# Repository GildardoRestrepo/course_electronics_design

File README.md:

# Diseño Electrónico — UPB

Este repositorio reúne todas las actividades del curso **Diseño Electrónico** (UPB). El curso combina una parte **teórica sobre inteligencia artificial** y una parte **práctica sobre IoT, sistemas embebidos y diseño electrónico**: firmware para ESP32, servidores MQTT, dashboards y diseño de PCB en KiCad.

**Autor:** Gildardo Estevan Restrepo Duque

## Actividades

| #   | Actividad                                                                                       | Carpeta                                                | Bitácora                                                               |
| --- | ----------------------------------------------------------------------------------------------- | ------------------------------------------------------ | ---------------------------------------------------------------------- |
| 01  | Conexión a Ubidots                                                                              | [`01_ubidots_connection`](01_ubidots_connection)       | [01_ubidots_connection.md](00_docs/01_ubidots_connection.md)           |
| 02  | Suscripción a Ubidots (downlinks)                                                               | [`02_ubidots_subscription`](02_ubidots_subscription)   | [02_ubidots_subscription.md](00_docs/02_ubidots_subscription.md)       |
| 03  | Access Point + servidor web                                                                     | [`03_webserver_accesspoint`](03_webserver_accesspoint) | [03_webserver_accesspoint.md](00_docs/03_webserver_accesspoint.md)     |
| 04  | Repositorio de entregables                                                                      | —                                                      | [04_repositorio_entregables.md](00_docs/04_repositorio_entregables.md) |
| 05  | MQTT local: Mosquitto + Node-RED                                                                | [`05_mqtt_local_nodered`](05_mqtt_local_nodered)       | [05_mqtt_local_nodered.md](00_docs/05_mqtt_local_nodered.md)           |
| 06  | MQTT en la nube: AWS + Mosquitto + Node-RED                                                     | [`06_mqtt_in_aws`](06_mqtt_in_aws)                     | [06_mqtt_in_aws.md](00_docs/06_mqtt_in_aws.md)                         |
| 08  | Introducción al flujo de trabajo en KiCad                                                       | [`08_kicad_flow_work`](08_kicad_flow_work)             | [08_kicad_flow_work.md](00_docs/08_kicad_flow_work.md)                 |
| 09  | Fuente de poder en KiCad                                                                        | [`09_power_supply`](09_power_supply)                   | [09_power_supply.md](00_docs/09_power_supply.md)                       |
| 10  | Diseño en 4 capas: datalogger ATmega328P                                                        | [`10_4layer_design`](10_4layer_design)                 | [10_4layer_design.md](00_docs/10_4layer_design.md)                     |
| 11  | Diseño de placa basada en ESP32:<br>Controlador de Conmutación para Semiconductores de Potencia | `11_final_esp32`                                       | [[11_gating_block_power_electronics]]                                  |

Cada bitácora de [`00_docs/`](00_docs) explica el objetivo, el montaje y cómo reproducir la práctica. Los valores reales de Wi-Fi, tokens y contraseñas no se versionan: cada proyecto trae un archivo de ejemplo (`secrets.h.example`) o marcadores para completar localmente.

La carpeta [`.claude/skills/kicad-flow`](.claude/skills/kicad-flow) contiene el flujo de trabajo para diseñar y verificar los proyectos de KiCad con Claude Code.

## Licencia

MIT. Ver [LICENSE](LICENSE).

---
## Enlaces
[[diseno_electronico_iot|Diseño Electrónico IoT]]

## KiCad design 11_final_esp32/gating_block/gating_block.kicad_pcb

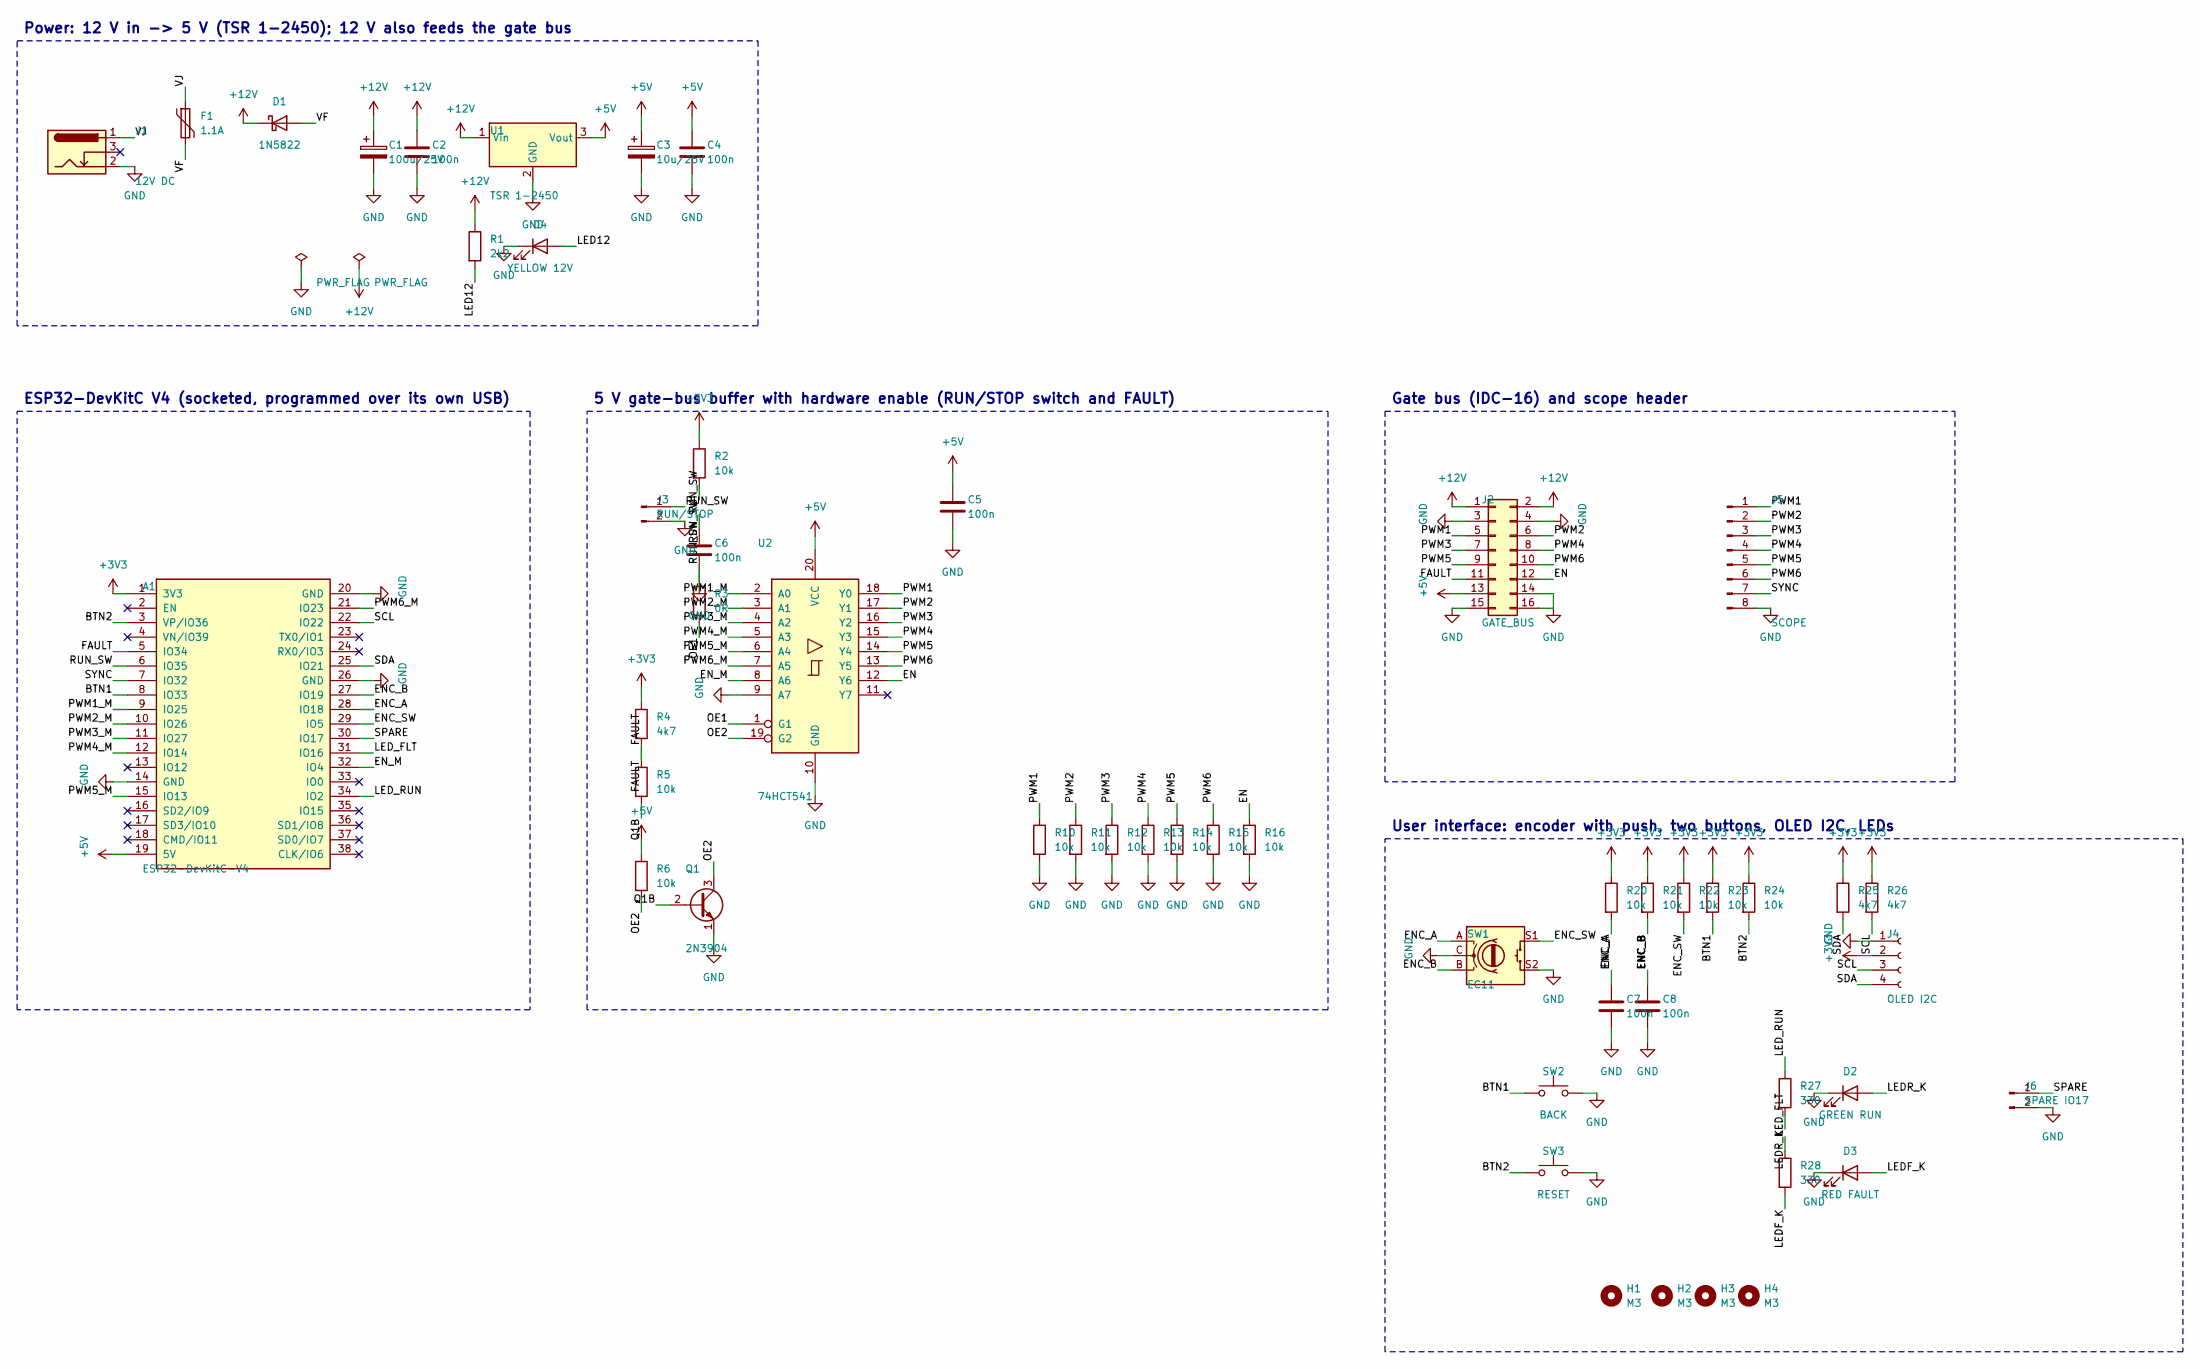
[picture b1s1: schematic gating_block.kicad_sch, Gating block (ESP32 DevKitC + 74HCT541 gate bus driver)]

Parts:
A1: ESP32-DevKitC-V4; ESP32-DevKitC-V4_Socket
C1: 100u/25V; C_Radial_D8.0mm_H11.5mm_P3.50mm
C2, C4, C5, C6, C7, C8: 100n; C_Disc_D5.0mm_W2.5mm_P5.00mm
C3: 10u/25V; C_Radial_D5.0mm_H11.0mm_P2.00mm
D1: 1N5822; D_DO-201AD_P15.24mm_Horizontal
D2: GREEN RUN; LED_D3.0mm
D3: RED FAULT; LED_D3.0mm
D4: YELLOW 12V; LED_D3.0mm
F1: 1.1A; Fuse_Bourns_MF-RG1100
H1, H2, H3, H4: M3; MountingHole_3.2mm_M3
J1: 12V DC; BarrelJack_Horizontal
J2: GATE_BUS; IDC-Header_2x08-1MP_P2.54mm_Latch9.5mm_Vertical
J3: RUN/STOP; PinHeader_1x02_P2.54mm_Vertical
J4: OLED I2C; PinSocket_1x04_P2.54mm_Vertical
J5: SCOPE; PinHeader_1x08_P2.54mm_Vertical
J6: SPARE IO17; PinHeader_1x02_P2.54mm_Vertical
Q1: 2N3904; TO-92_Inline
R1: 2k2; R_Axial_DIN0207_L6.3mm_D2.5mm_P10.16mm_Horizontal
R2, R5, R6, R10, R11, R12, R13, R14, R15, R16, R20, R21, R22, R23, R24: 10k; R_Axial_DIN0207_L6.3mm_D2.5mm_P10.16mm_Horizontal
R3: 0R; R_Axial_DIN0207_L6.3mm_D2.5mm_P10.16mm_Horizontal
R4, R25, R26: 4k7; R_Axial_DIN0207_L6.3mm_D2.5mm_P10.16mm_Horizontal
R27, R28: 330; R_Axial_DIN0207_L6.3mm_D2.5mm_P10.16mm_Horizontal
SW1: EC11; RotaryEncoder_Alps_EC11E-Switch_Vertical_H20mm
SW2: BACK; SW_PUSH_6mm_H13mm
SW3: RESET; SW_PUSH_6mm_H13mm
U1: TSR 1-2450; Converter_DCDC_TRACO_TSR-1_THT
U2: 74HCT541; DIP-20_W7.62mm

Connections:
+3V3: A1.1 (3V3), J4.2, R2.1, R4.1, R20.1, R21.1, R22.1, R23.1, R24.1, R25.1, R26.1
+5V: A1.19 (5V), C3.1, C4.1, C5.1, J2.13, R6.1, U1.3 (Vout), U2.20 (VCC)
+12V: C1.1, C2.1, D1.1 (K), J2.1, J2.2, R1.1, U1.1 (Vin)
/BTN1: A1.8 (IO33), R23.2, SW2.1
/BTN2: A1.3 (VP/IO36), R24.2, SW3.1
/EN: J2.12, R16.1, U2.12 (Y6)
/ENC_A: A1.28 (IO18), C7.1, R20.2, SW1.A
/ENC_B: A1.27 (IO19), C8.1, R21.2, SW1.B
/ENC_SW: A1.29 (IO5), R22.2, SW1.S1
/EN_M: A1.32 (IO4), U2.8 (A6)
/FAULT: A1.5 (IO34), J2.11, R4.2, R5.1
/LED12: D4.2 (A), R1.2
/LEDF_K: D3.2 (A), R28.2
/LEDR_K: D2.2 (A), R27.2
/LED_FLT: A1.31 (IO16), R28.1
/LED_RUN: A1.34 (IO2), R27.1
/OE1: R3.2, U2.1 (G1)
/OE2: Q1.3 (C), R6.2, U2.19 (G2)
/PWM1: J2.5, J5.1, R10.1, U2.18 (Y0)
/PWM1_M: A1.9 (IO25), U2.2 (A0)
/PWM2: J2.6, J5.2, R11.1, U2.17 (Y1)
/PWM2_M: A1.10 (IO26), U2.3 (A1)
/PWM3: J2.7, J5.3, R12.1, U2.16 (Y2)
/PWM3_M: A1.11 (IO27), U2.4 (A2)
/PWM4: J2.8, J5.4, R13.1, U2.15 (Y3)
/PWM4_M: A1.12 (IO14), U2.5 (A3)
/PWM5: J2.9, J5.5, R14.1, U2.14 (Y4)
/PWM5_M: A1.15 (IO13), U2.6 (A4)
/PWM6: J2.10, J5.6, R15.1, U2.13 (Y5)
/PWM6_M: A1.21 (IO23), U2.7 (A5)
/Q1B: Q1.2 (B), R5.2
/RUN_SW: A1.6 (IO35), C6.1, J3.1, R2.2, R3.1
/SCL: A1.22 (IO22), J4.3, R26.2
/SDA: A1.25 (IO21), J4.4, R25.2
/SPARE: A1.30 (IO17), J6.1
/SYNC: A1.7 (IO32), J5.7
/VF: D1.2 (A), F1.2
/VJ: F1.1, J1.1
GND: A1.14 (GND), A1.20 (GND), A1.26 (GND), C1.2, C2.2, C3.2, C4.2, C5.2, C6.2, C7.2, C8.2, D2.1 (K), D3.1 (K), D4.1 (K), J1.2, J2.3, J2.4, J2.14, J2.15, J2.16, J3.2, J4.1, J5.8, J6.2, Q1.1 (E), R10.2, R11.2, R12.2, R13.2, R14.2, R15.2, R16.2, SW1.C, SW1.S2, SW2.2, SW3.2, U1.2 (GND), U2.9 (A7), U2.10 (GND)

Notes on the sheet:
Power: 12 V in -> 5 V (TSR 1-2450); 12 V also feeds the gate bus
ESP32-DevKitC V4 (socketed, programmed over its own USB)
5 V gate-bus buffer with hardware enable (RUN/STOP switch and FAULT)
Gate bus (IDC-16) and scope header
User interface: encoder with push, two buttons, OLED I2C, LEDs

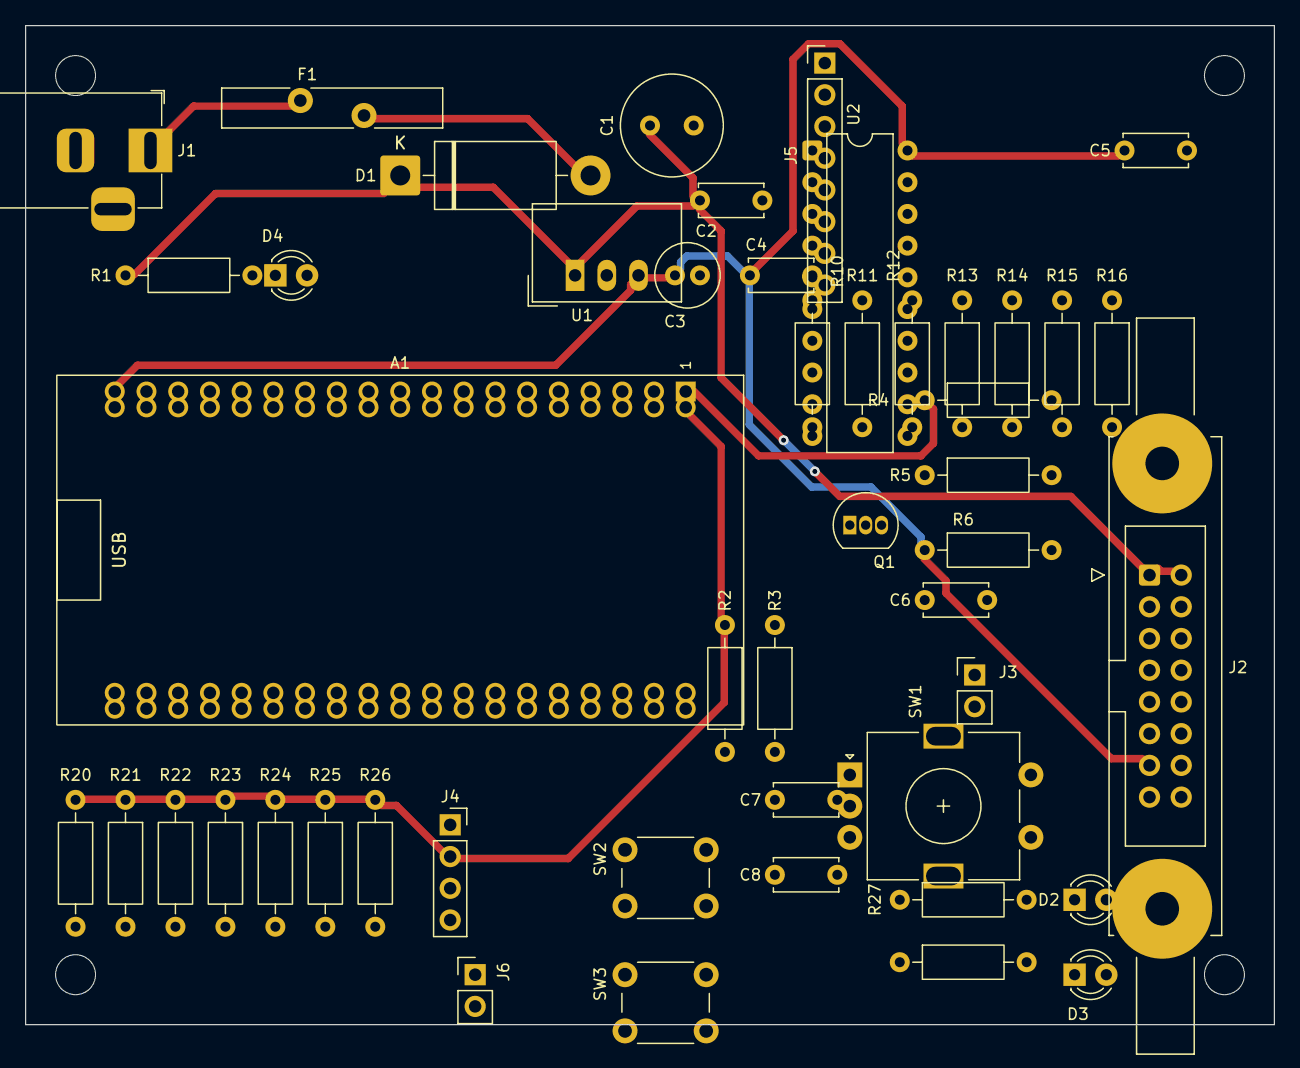
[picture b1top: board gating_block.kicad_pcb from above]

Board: 2 copper layers, 100.0 x 80.0 mm, 52 parts (0 on the bottom side), 39 nets.

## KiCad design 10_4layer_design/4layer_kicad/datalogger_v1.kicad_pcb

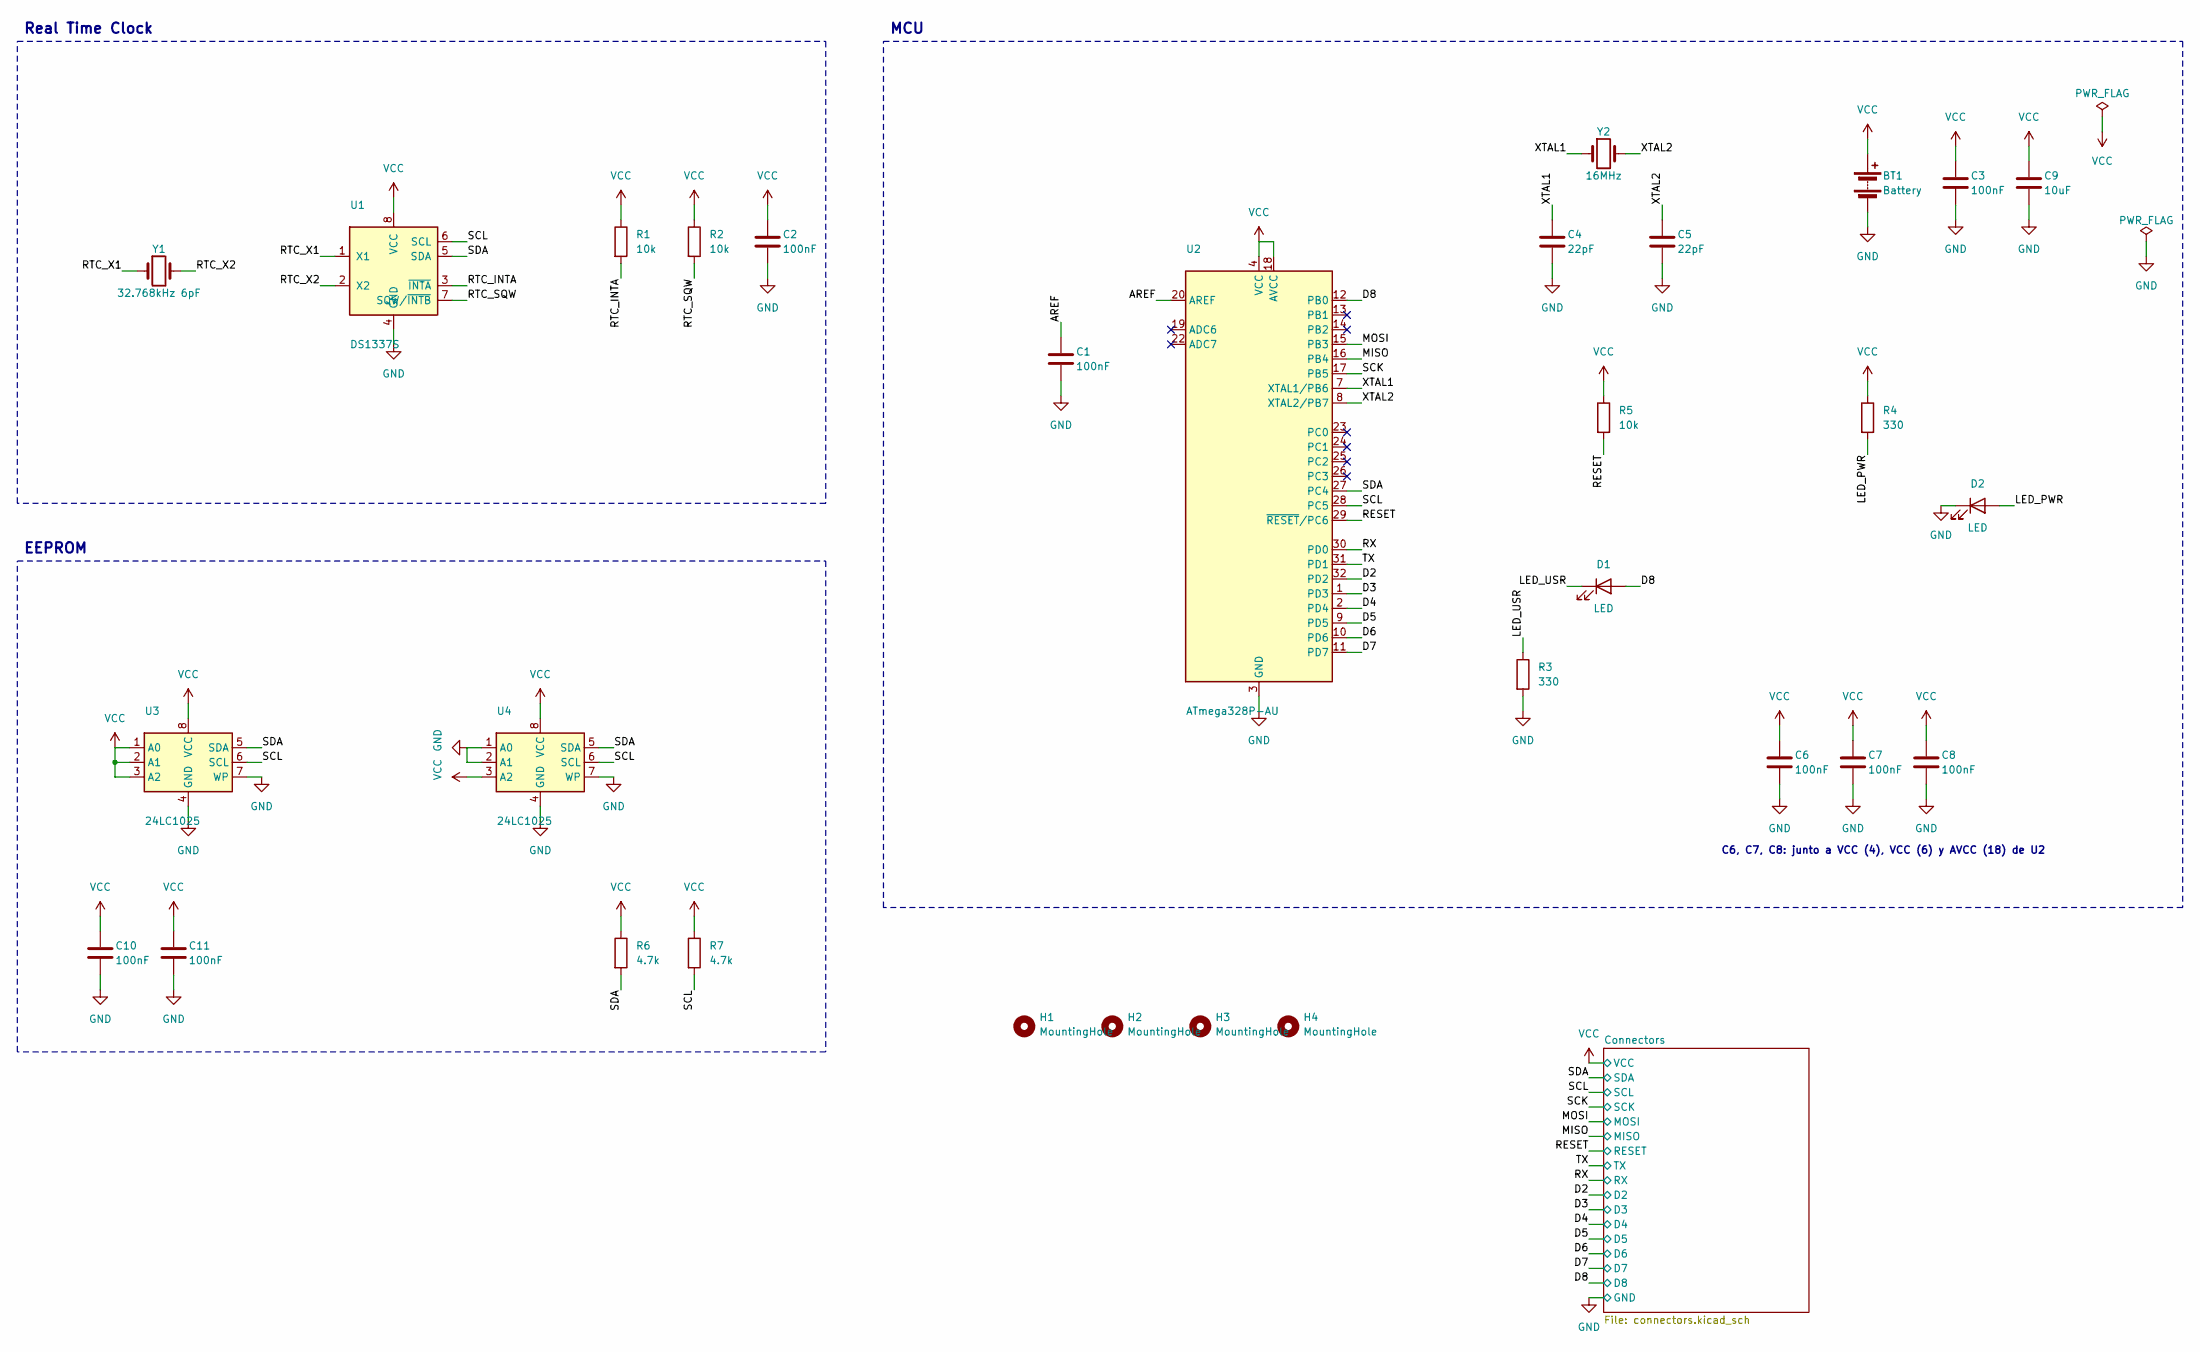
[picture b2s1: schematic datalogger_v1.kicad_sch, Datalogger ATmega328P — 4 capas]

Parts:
BT1: Battery; JST_PH_S2B-PH-K_1x02_P2.00mm_Horizontal
C1, C2, C3, C6, C7, C8, C10, C11: 100nF; C_0805_2012Metric
C4, C5: 22pF; C_0805_2012Metric
C9: 10uF; C_0805_2012Metric
D1, D2: LED; LED_0805_2012Metric
H1, H2, H3, H4: MountingHole; MountingHole_2.7mm_M2.5
R1, R2, R5: 10k; R_0805_2012Metric
R3, R4: 330; R_0805_2012Metric
R6, R7: 4.7k; R_0805_2012Metric
U1: DS1337S; SOIC-8_3.9x4.9mm_P1.27mm
U2: ATmega328P-AU; TQFP-32_7x7mm_P0.8mm
U3, U4: 24LC1025; SOIC-8_3.9x4.9mm_P1.27mm
Y1: 32.768kHz 6pF; Crystal_SMD_3215-2Pin_3.2x1.5mm
Y2: 16MHz; Crystal_SMD_HC49-SD

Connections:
/AREF: C1.1, U2.20 (AREF)
/D2: U2.32 (PD2); also elsewhere on the board
/D3: U2.1 (PD3); also elsewhere on the board
/D4: U2.2 (PD4); also elsewhere on the board
/D5: U2.9 (PD5); also elsewhere on the board
/D6: U2.10 (PD6); also elsewhere on the board
/D7: U2.11 (PD7); also elsewhere on the board
/D8: D1.2 (A), U2.12 (PB0); also elsewhere on the board
/LED_PWR: D2.2 (A), R4.2
/LED_USR: D1.1 (K), R3.1
/MISO: U2.16 (PB4); also elsewhere on the board
/MOSI: U2.15 (PB3); also elsewhere on the board
/RESET: R5.2, U2.29 (~RESET/PC6); also elsewhere on the board
/RTC_INTA: R1.2, U1.3 (~INTA)
/RTC_SQW: R2.2, U1.7 (SQW/~INTB)
/RTC_X1: U1.1 (X1), Y1.1
/RTC_X2: U1.2 (X2), Y1.2
/RX: U2.30 (PD0); also elsewhere on the board
/SCK: U2.17 (PB5); also elsewhere on the board
/SCL: R7.2, U1.6 (SCL), U2.28 (PC5), U3.6 (SCL), U4.6 (SCL); also elsewhere on the board
/SDA: R6.2, U1.5 (SDA), U2.27 (PC4), U3.5 (SDA), U4.5 (SDA); also elsewhere on the board
/TX: U2.31 (PD1); also elsewhere on the board
/XTAL1: C4.1, U2.7 (XTAL1/PB6), Y2.1
/XTAL2: C5.1, U2.8 (XTAL2/PB7), Y2.2
GND: BT1.2 (-), C1.2, C2.2, C3.2, C4.2, C5.2, C6.2, C7.2, C8.2, C9.2, C10.2, C11.2, D2.1 (K), R3.2, U1.4 (GND), U2.3 (GND), U2.5 (GND), U2.21 (GND), U3.4 (GND), U3.7 (WP), U4.1 (A0), U4.2 (A1), U4.4 (GND), U4.7 (WP); also elsewhere on the board
VCC: BT1.1 (+), C2.1, C3.1, C6.1, C7.1, C8.1, C9.1, C10.1, C11.1, R1.1, R2.1, R4.1, R5.1, R6.1, R7.1, U1.8 (VCC), U2.4 (VCC), U2.6 (VCC), U2.18 (AVCC), U3.1 (A0), U3.2 (A1), U3.3 (A2), U3.8 (VCC), U4.3 (A2), U4.8 (VCC); also elsewhere on the board

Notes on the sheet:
C6, C7, C8: junto a VCC (4), VCC (6) y AVCC (18) de U2
MCU
Real Time Clock
EEPROM

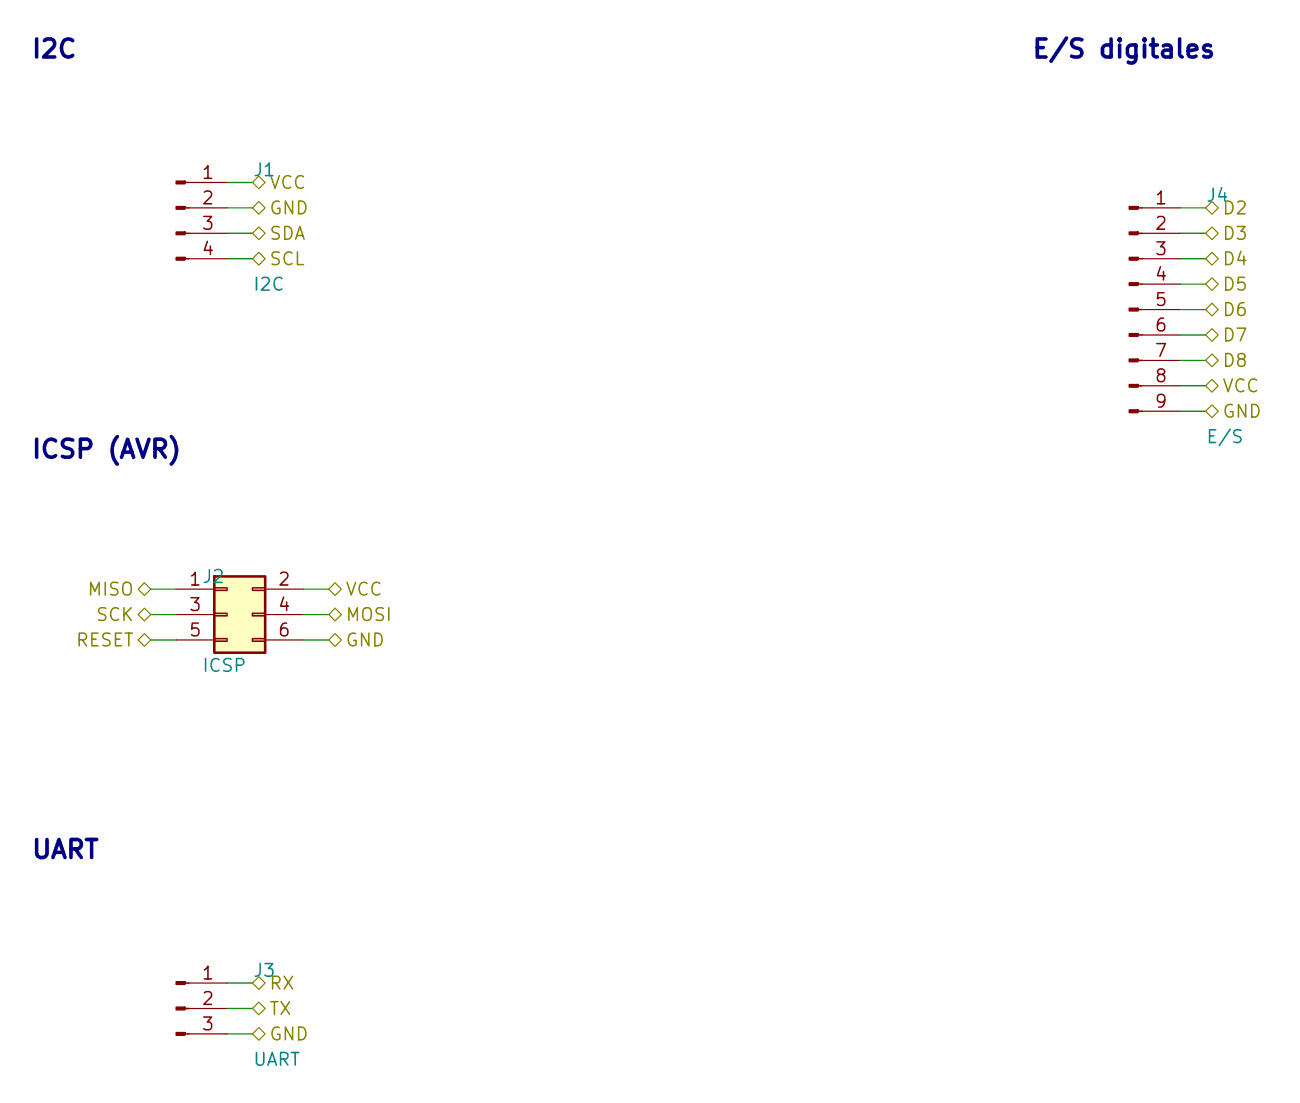
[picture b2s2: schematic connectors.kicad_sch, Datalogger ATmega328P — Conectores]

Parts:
J1: I2C; PinHeader_1x04_P2.54mm_Horizontal
J2: ICSP; PinHeader_2x03_P2.54mm_Vertical
J3: UART; PinHeader_1x03_P2.54mm_Horizontal
J4: E/S; PinHeader_1x09_P2.54mm_Vertical

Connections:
/D2: J4.1; also elsewhere on the board
/D3: J4.2; also elsewhere on the board
/D4: J4.3; also elsewhere on the board
/D5: J4.4; also elsewhere on the board
/D6: J4.5; also elsewhere on the board
/D7: J4.6; also elsewhere on the board
/D8: J4.7; also elsewhere on the board
/MISO: J2.1; also elsewhere on the board
/MOSI: J2.4; also elsewhere on the board
/RESET: J2.5; also elsewhere on the board
/RX: J3.1; also elsewhere on the board
/SCK: J2.3; also elsewhere on the board
/SCL: J1.4; also elsewhere on the board
/SDA: J1.3; also elsewhere on the board
/TX: J3.2; also elsewhere on the board
GND: J1.2, J2.6, J3.3, J4.9; also elsewhere on the board
VCC: J1.1, J2.2, J4.8; also elsewhere on the board

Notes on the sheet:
E/S digitales
I2C
ICSP (AVR)
UART

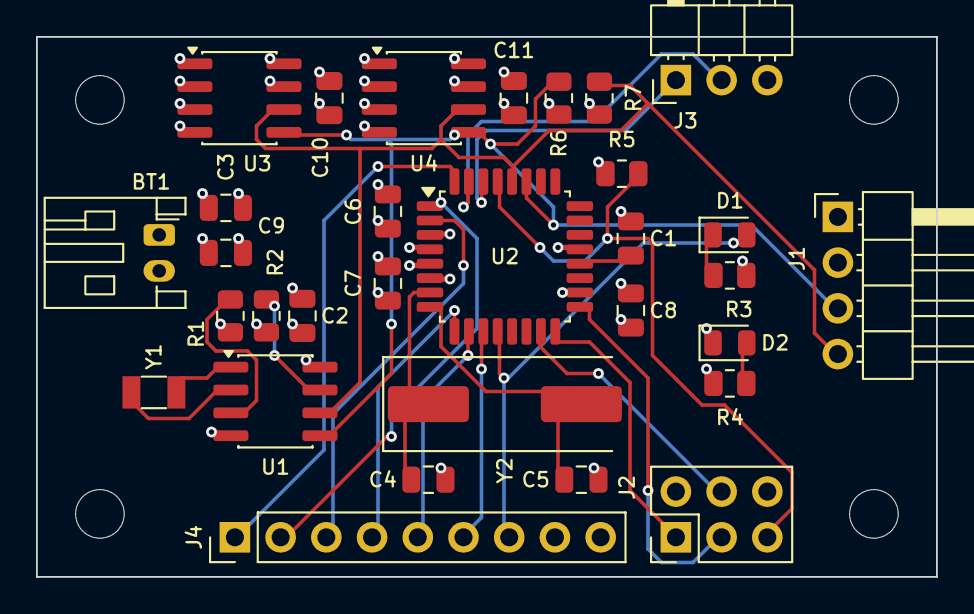
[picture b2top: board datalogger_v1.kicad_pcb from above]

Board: 4 copper layers, 50.0 x 30.0 mm, 35 parts (0 on the bottom side), 26 nets.

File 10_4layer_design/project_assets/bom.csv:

"Reference","Value","Footprint","QUANTITY"
"BT1","Battery","Connector_JST:JST_PH_S2B-PH-K_1x02_P2.00mm_Horizontal","1"
"C1,C2,C3,C6,C7,C8,C10,C11","100nF","Capacitor_SMD:C_0805_2012Metric","8"
"C4,C5","22pF","Capacitor_SMD:C_0805_2012Metric","2"
"C9","10uF","Capacitor_SMD:C_0805_2012Metric","1"
"D1,D2","LED","LED_SMD:LED_0805_2012Metric","2"
"J1","I2C","Connector_PinHeader_2.54mm:PinHeader_1x04_P2.54mm_Horizontal","1"
"J2","ICSP","Connector_PinHeader_2.54mm:PinHeader_2x03_P2.54mm_Vertical","1"
"J3","UART","Connector_PinHeader_2.54mm:PinHeader_1x03_P2.54mm_Horizontal","1"
"J4","E/S","Connector_PinHeader_2.54mm:PinHeader_1x09_P2.54mm_Vertical","1"
"R1,R2,R5","10k","Resistor_SMD:R_0805_2012Metric","3"
"R3,R4","330","Resistor_SMD:R_0805_2012Metric","2"
"R6,R7","4.7k","Resistor_SMD:R_0805_2012Metric","2"
"U1","DS1337S","Package_SO:SOIC-8_3.9x4.9mm_P1.27mm","1"
"U2","ATmega328P-AU","Package_QFP:TQFP-32_7x7mm_P0.8mm","1"
"U3,U4","24LC1025","Package_SO:SOIC-8_3.9x4.9mm_P1.27mm","2"
"Y1","32.768kHz 6pF","Crystal:Crystal_SMD_3215-2Pin_3.2x1.5mm","1"
"Y2","16MHz","Crystal:Crystal_SMD_HC49-SD","1"
